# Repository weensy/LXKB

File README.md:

<p align="center">

<p>
<h2 align="center">60% Mechanical Keyboard</h1>
  
LXKB is an open-source project that makes minimal keyboard with 60 keys.

# Introduction

### Who is it for?
For coders, writers and for everyone.  
This allows for fast typing with minimal movement.
In addition, it minimizes the burden on the shoulder even for long time use.
You should use a minimal keyboard for shoulder health.
A 60% keyboard is best for that.  
So, is LXKB different from the normal 60% keyboard?
It's in the aesthetics of this keyboard.

### Aesthetics
is realized in Symmetry.  
The following is the layout of LXKB for Windows. *[*see more layouts](layout.md)*
<p align="center">

<p>

It is a completely symmetrical design.  
Draw a line in the center:
<p align="center">

<p>

Row 1, 2 are diagonally symmetric. And row 3 to 5 are perfectly symmetrical.
As is known, most people feel psychologically secure in symmetry.

### Feature
The most striking feature is the position of the Fn key.
The usage of Caps lock is very infrequent. But among the non-letter keys, it is located in the most convenient place to press. This place is a waste for Caps lock! It is why we put Fn key here.  
We have placed the rest of combination keys where comfortable to press.
People place their hands diagonally on the keyboard for body structural reasons. Therefore, the range of keys that can be pressed by moving only a finger from the default position is as follow:
<p align="center">

<p>
Blue is left hand, red is right hand. Since the left hand presses the Fn key, the combination keys are placed in the red range. Here is the result:
<p align="center">

<p>

### Inspired by
This layout is inspried by [these keyboards](./inspired.md).

### Keycaps
This layout is not standard, so be careful when buying keycaps.  
[Here](./keycaps.md) is a list of compatible keycap sets.

# Goals
We want to provide sources for making keyboards that is:
- Gerber files for ordering PCB
- Draw files for ordering Case
- Keymap.json file for QMK Configurator
- Documentation for ordering, assembly and setting from zero to finished product

# Contribute
Do you want to help? That’s awesome. We welcome contributions of all kinds from everyone.

# Open-source
The following open-source software was used for this project. Thanks for everything:
- [Keyboard Layout Editor](http://www.keyboard-layout-editor.com/)
- [Keyboard tools](http://keyboard-tools.xyz/)
- [Freerouting](https://github.com/freerouting/freerouting)

# License
Licensed under the [CC BY-NC-SA 4.0](./LICENSE).  
Almost everything is permitted, but not for commercial use.

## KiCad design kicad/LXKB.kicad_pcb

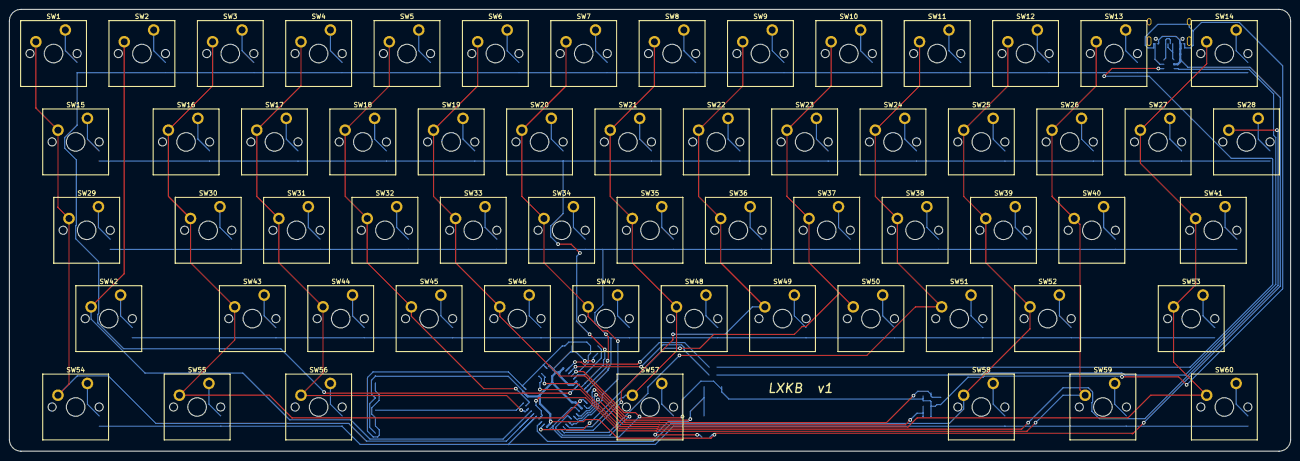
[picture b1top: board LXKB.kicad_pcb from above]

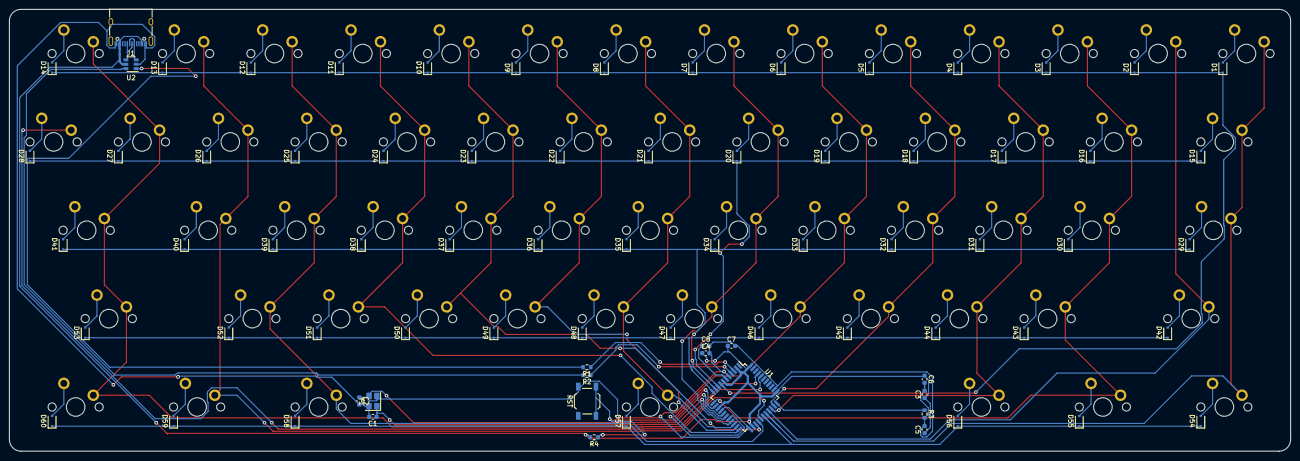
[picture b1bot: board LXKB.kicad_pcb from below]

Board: 2 copper layers, 276.2 x 95.2 mm, 137 parts (77 on the bottom side), 93 nets.

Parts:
C1, C2: 22p; C_0603_1608Metric
C3, C4, C5, C6: 0.1u; C_0603_1608Metric
C7: 4.7u; C_0603_1608Metric
C8: 1u; C_0603_1608Metric
D1, D2, D3, D4, D5, D6, D7, D8, D9, D10, D11, D12, D13, D14, D15, D16, D17, D18, D19, D20, D21, D22, D23, D24, D25, D26, D27, D28, D29, D30, D31, D32, D33, D34, D35, D36, D37, D38, D39, D40, D41, D42, D43, D44, D45, D46, D47, D48, D49, D50, D51, D52, D53, D54, D55, D56, D57, D58, D59, D60: D; D_SOD-323F
J1: USB_C_Receptacle_USB2.0; USB_C_Receptacle_XKB_U262-16XN-4BVC11
R1, R2: 22; R_0603_1608Metric
R3, R4: 10k; R_0603_1608Metric
RST: SW_SPST; SW_SPST_TL3342
SW1, SW2, SW3, SW4, SW5, SW6, SW7, SW8, SW9, SW10, SW11, SW12, SW13, SW16, SW17, SW18, SW19, SW20, SW21, SW22, SW23, SW24, SW25, SW26, SW27, SW28, SW30, SW31, SW32, SW33, SW34, SW35, SW36, SW37, SW38, SW39, SW40, SW43, SW44, SW45, SW46, SW47, SW48, SW49, SW50, SW51, SW52: SW_Push; SW_Cherry_MX_PCB_1.00u
SW14, SW15, SW54, SW56, SW58, SW60: SW_Push; SW_Cherry_MX_PCB_1.50u
SW29, SW41: SW_Push; SW_Cherry_MX_PCB_1.75u
SW42, SW53: SW_Push; SW_Cherry_MX_PCB_2.25u
SW55, SW59: SW_Push; SW_Cherry_MX_PCB_1.25u
SW57: SW_Push; SW_Cherry_MX_PCB_6.00u
U1: ATmega16U4-AU; TQFP-44_10x10mm_P0.8mm
U2: TPD2S017; SOT-23-6
Y1: Crystal_GND24; Crystal_SMD_3225-4Pin_3.2x2.5mm

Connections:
COL0: SW1.1, SW15.1, SW29.1, SW54.1, U1.29
COL1: SW2.1, SW42.1, U1.30
COL2: SW3.1, SW16.1, SW30.1, SW43.1, SW55.1, U1.12
COL3: SW4.1, SW17.1, SW31.1, SW44.1, SW56.1, U1.31
COL4: SW5.1, SW18.1, SW32.1, SW45.1, U1.32
COL5: SW6.1, SW19.1, SW33.1, SW46.1, U1.18
COL6: SW7.1, SW20.1, SW34.1, SW47.1, U1.19
COL7: SW8.1, SW21.1, SW35.1, SW48.1, SW57.1, U1.20
COL8: SW9.1, SW22.1, SW36.1, SW49.1, U1.21
COL9: SW10.1, SW23.1, SW37.1, SW50.1, U1.25
COL10: SW11.1, SW24.1, SW38.1, SW51.1, U1.22
COL11: SW12.1, SW25.1, SW39.1, SW52.1, SW58.1, U1.26
COL12: SW13.1, SW26.1, SW40.1, SW59.1, U1.27
COL13: SW14.1, SW27.1, SW41.1, SW53.1, SW60.1, U1.41
COL14: SW28.1, U1.40
GND: C1.2, C2.2, C3.2, C4.2, C5.2, C6.2, C7.2, C8.2, J1.A1, J1.A12, J1.B1, J1.B12, J1.S1, R3.2, RST.1, U1.5, U1.15, U1.23, U1.35, U1.43, U2.2, Y1.2, Y1.4
unnamed: D1.2, SW1.2
unnamed: D2.2, SW2.2
unnamed: D3.2, SW3.2
unnamed: D4.2, SW4.2
unnamed: D5.2, SW5.2
unnamed: D6.2, SW6.2
unnamed: D7.2, SW7.2
unnamed: D8.2, SW8.2
unnamed: D9.2, SW9.2
unnamed: D10.2, SW10.2
unnamed: D11.2, SW11.2
unnamed: D12.2, SW12.2
unnamed: D13.2, SW13.2
unnamed: D14.2, SW14.2
unnamed: D15.2, SW15.2
unnamed: D16.2, SW16.2
unnamed: D17.2, SW17.2
unnamed: D18.2, SW18.2
unnamed: D19.2, SW19.2
unnamed: D20.2, SW20.2
unnamed: D21.2, SW21.2
unnamed: D22.2, SW22.2
unnamed: D23.2, SW23.2
unnamed: D24.2, SW24.2
unnamed: D25.2, SW25.2
unnamed: D26.2, SW26.2
unnamed: D27.2, SW27.2
unnamed: D28.2, SW28.2
unnamed: D29.2, SW29.2
unnamed: D30.2, SW30.2
unnamed: D31.2, SW31.2
unnamed: D32.2, SW32.2
unnamed: D33.2, SW33.2
unnamed: D34.2, SW34.2
unnamed: D35.2, SW35.2
unnamed: D36.2, SW36.2
unnamed: D37.2, SW37.2
unnamed: D38.2, SW38.2
unnamed: D39.2, SW39.2
unnamed: D40.2, SW40.2
unnamed: D41.2, SW41.2
unnamed: D42.2, SW42.2
unnamed: D43.2, SW43.2
unnamed: D44.2, SW44.2
unnamed: D45.2, SW45.2
unnamed: D46.2, SW46.2
unnamed: D47.2, SW47.2
unnamed: D48.2, SW48.2
unnamed: D49.2, SW49.2
unnamed: D50.2, SW50.2
unnamed: D51.2, SW51.2
unnamed: D52.2, SW52.2
unnamed: D53.2, SW53.2
unnamed: D54.2, SW54.2
unnamed: D55.2, SW55.2
unnamed: D56.2, SW56.2
unnamed: D57.2, SW57.2
unnamed: D58.2, SW58.2
unnamed: D59.2, SW59.2
unnamed: D60.2, SW60.2
ROW0: D1.1, D2.1, D3.1, D4.1, D5.1, D6.1, D7.1, D8.1, D9.1, D10.1, D11.1, D12.1, D13.1, D14.1, U1.8
ROW1: D15.1, D16.1, D17.1, D18.1, D19.1, D20.1, D21.1, D22.1, D23.1, D24.1, D25.1, D26.1, D27.1, D28.1, U1.9
ROW2: D29.1, D30.1, D31.1, D32.1, D33.1, D34.1, D35.1, D36.1, D37.1, D38.1, D39.1, D40.1, D41.1, U1.10
ROW3: D42.1, D43.1, D44.1, D45.1, D46.1, D47.1, D48.1, D49.1, D50.1, D51.1, D52.1, D53.1, U1.11
ROW4: D54.1, D55.1, D56.1, D57.1, D58.1, D59.1, D60.1, U1.28
VCC: C3.1, C4.1, C5.1, C6.1, C7.1, J1.A4, J1.A9, J1.B4, J1.B9, R4.2, U1.2, U1.7, U1.14, U1.24, U1.34, U1.44, U2.5
mcu/D+: R2.1, U1.4
mcu/D-: R1.1, U1.3
mcu/UCAP: C8.1, U1.6
mcu/XTAL1: C1.1, U1.17, Y1.1
mcu/XTAL2: C2.1, U1.16, Y1.3
mcu/~HWB~/PE2: R3.1, U1.33
mcu/~RESET: R4.1, RST.2, U1.13
u2/D+: R2.2, U2.6
u2/D-: R1.2, U2.1
usb/D+: J1.A6, J1.B6, U2.4
usb/D-: J1.A7, J1.B7, U2.3

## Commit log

2021-06-18 Create LICENSE
    CC BY-NC-SA 4.0
2021-06-19 Add default json and readme
2021-06-19 Add images
2021-10-07 Add logo.png
2021-10-10 Add inspired
2021-10-11 Add layout.md
2021-10-11 Remove json
2021-10-11 Fix link url in README.md
2021-10-13 Add KiCAD project
2021-10-17 Fix typo in README.md
2021-10-26 Add keycaps.md
2021-11-10 Add gitignore
2021-11-10 Route PCB
2021-11-12 Add rounding to edgecut of PCB
2023-01-02 Remove .DS_Store
